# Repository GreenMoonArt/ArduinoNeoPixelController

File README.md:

# ArduinoNeoPixelController
Arduino NeoPixel PCB

Eagle CAD files for a PCB that holds an Arduino Pro Mini, power connections, an analog input, and outputs for up to 6 NeoPixel LED strands.

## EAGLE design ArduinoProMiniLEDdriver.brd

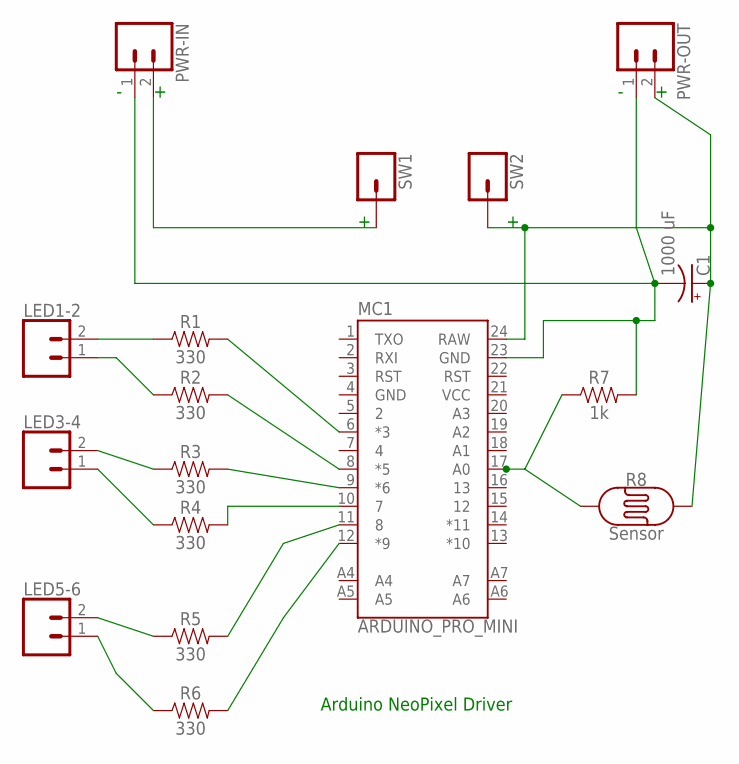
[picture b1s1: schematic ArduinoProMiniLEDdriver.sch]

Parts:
C1: 1000 uF; CPOL-RADIAL-5MM-10MM
LED1-2, LED3-4, LED5-6: CONN_025MM; SCREWTERMINAL-5MM-2
MC1: ARDUINO_PRO_MINI
PWR-IN: CONN_025MM; SCREWTERMINAL-5MM-2
PWR-OUT: CONN_025MM; SCREWTERMINAL-5MM-2
R1, R2, R3, R4, R5, R6: 330; AXIAL-0.3
R7: 1k; AXIAL-0.3
R8: Sensor; PHOTOCELL
SW1, SW2: CONN_01; 1X01

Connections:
GND: C1.-, MC1.4 (GND), MC1.23 (GND), PWR-IN.1, PWR-OUT.1, R7.P$2 (2)
unnamed: MC1.6 (*3), R1.P$2 (2)
unnamed: MC1.8 (*5), R2.P$2 (2)
unnamed: MC1.9 (*6), R3.P$2 (2)
unnamed: MC1.10 (7), R4.P$2 (2)
unnamed: LED1-2.2, R1.P$1 (1)
unnamed: LED1-2.1, R2.P$1 (1)
unnamed: LED3-4.2, R3.P$1 (1)
unnamed: LED3-4.1, R4.P$1 (1)
unnamed: LED5-6.2, R5.P$1 (1)
unnamed: LED5-6.1, R6.P$1 (1)
unnamed: C1.+, MC1.24 (RAW), PWR-OUT.2, R8.2, SW2.1
unnamed: PWR-IN.2, SW1.1
unnamed: MC1.17 (A0), R7.P$1 (1), R8.1
unnamed: MC1.11 (8), R5.P$2 (2)
unnamed: MC1.12 (*9), R6.P$2 (2)
VCC: MC1.21 (VCC)

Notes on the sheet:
Arduino NeoPixel Driver

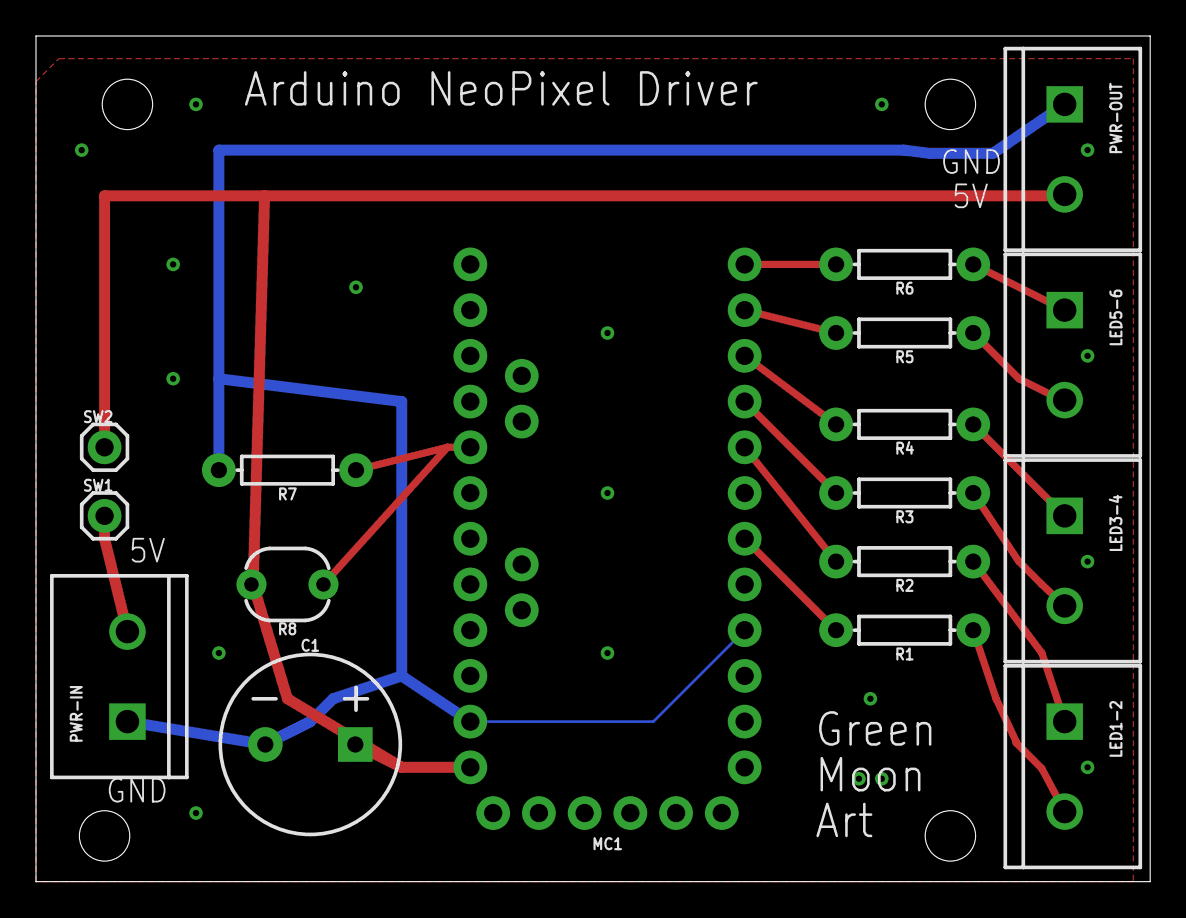
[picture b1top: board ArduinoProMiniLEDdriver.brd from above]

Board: 2 copper layers, 61.9 x 47.0 mm, 17 parts (0 on the bottom side), 16 nets.

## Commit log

2018-02-21 Eagle CAD PCB Board Layout
    Power input, switch, analog sensor (such as a photo resistor) and voltage divider resistor, 1000 uF capacitor, Arduino Pro Mini, 6 digital outputs connected via 220 Ohm resistors to screw terminal bl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
2018-02-21 Eagle CAD Schematic
2018-02-21 Example Arduino Sketch using NeoPixel PCB
    This sketch takes advantage of the PCB design by using a photo resistor to determine nightfall, and several NeoPixel strand outputs.
2018-02-21 PCB Image

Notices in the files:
parts and their libraries:
SparkFun-Capacitors: Licensing: Creative Commons ShareAlike 4.0 International - https://creativecommons.org/licenses/by-sa/4.0
